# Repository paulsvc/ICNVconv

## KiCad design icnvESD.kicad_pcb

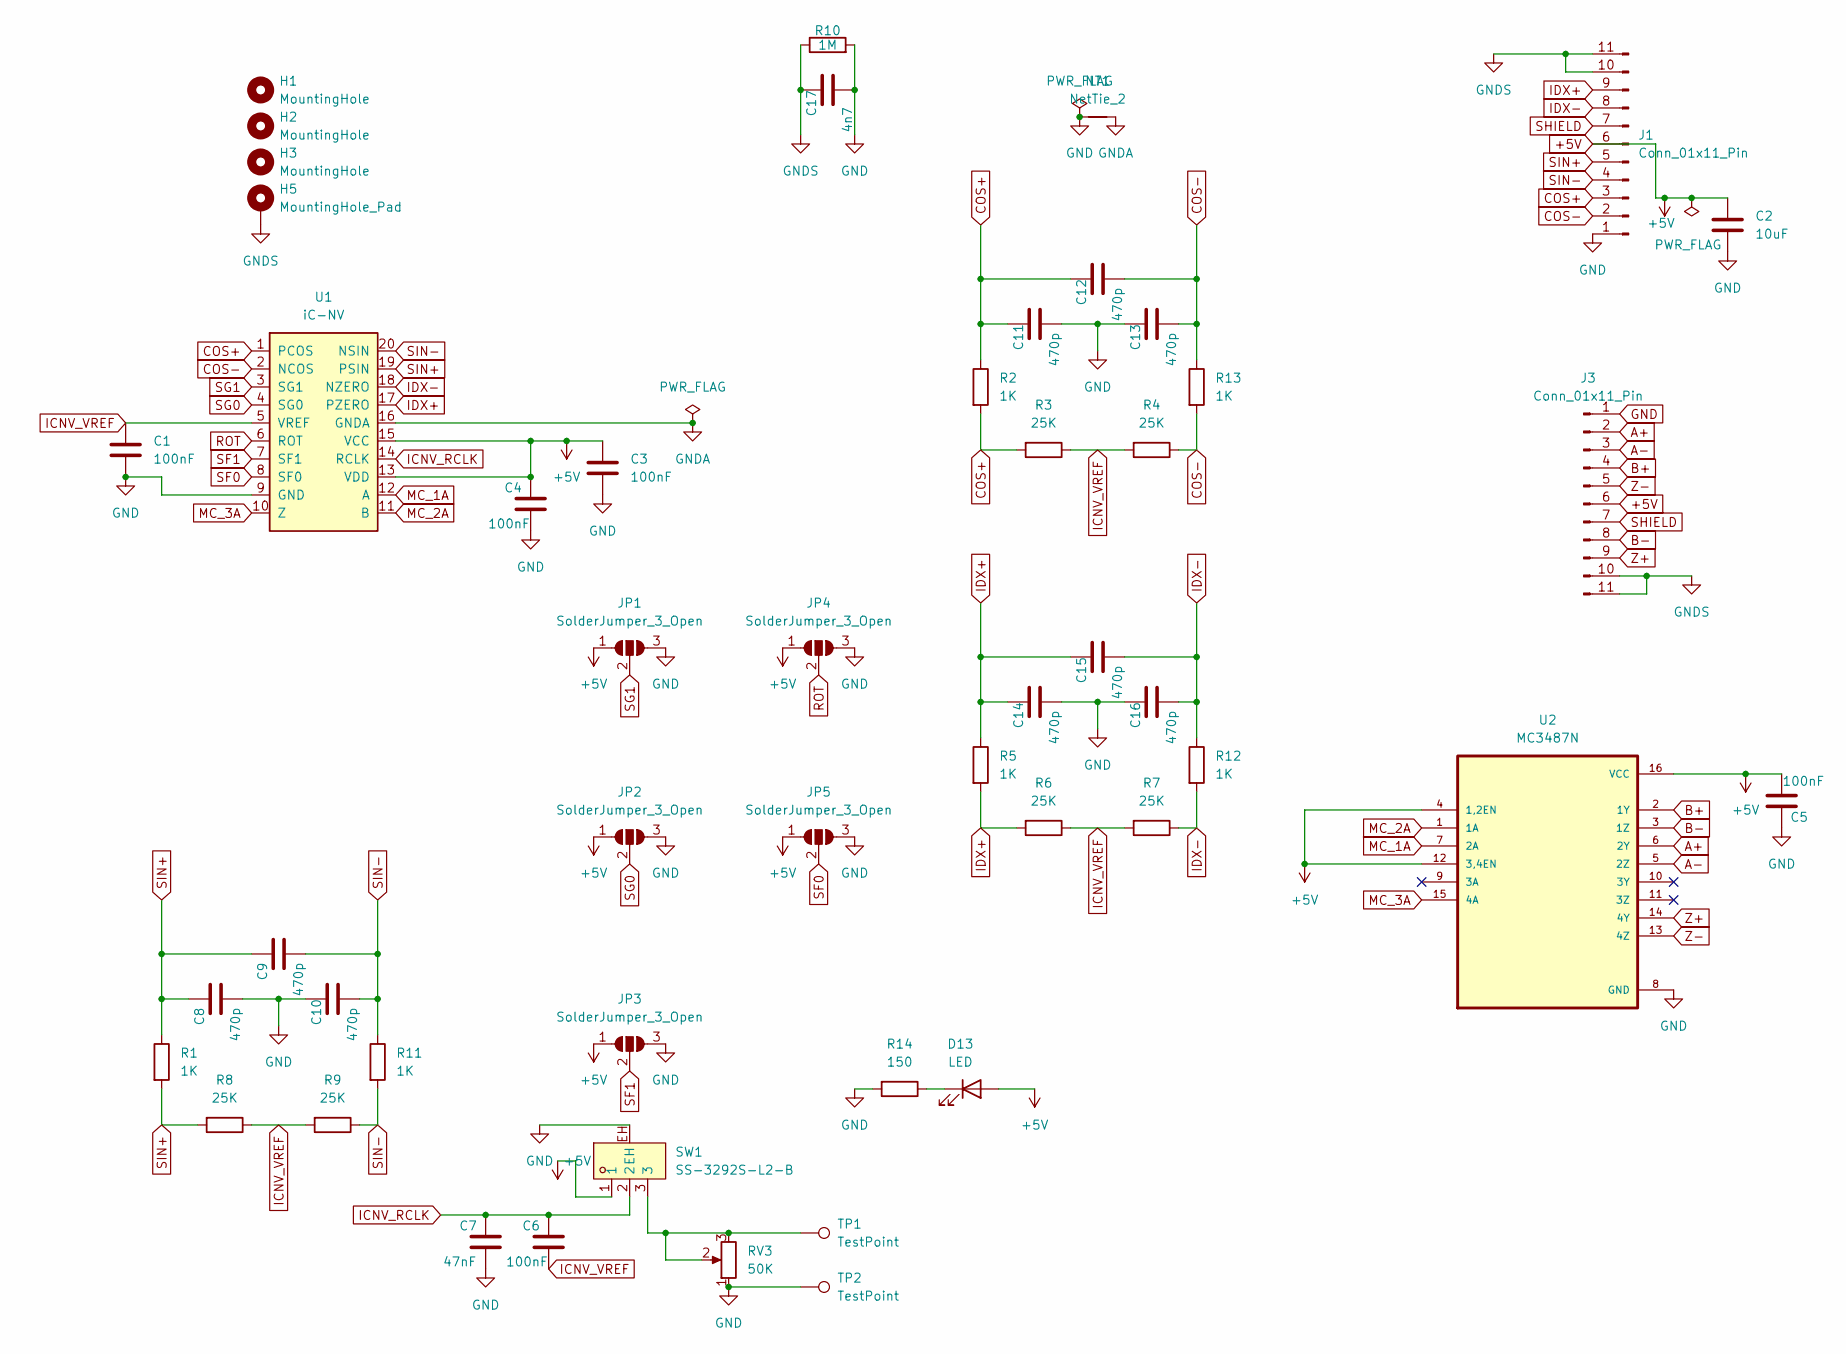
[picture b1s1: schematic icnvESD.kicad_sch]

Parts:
C1, C3, C4, C5, C6: 100nF; C_0603_1608Metric_Pad1.08x0.95mm_HandSolder
C2: 10uF; C_0603_1608Metric_Pad1.08x0.95mm_HandSolder
C7: 47nF; C_0603_1608Metric_Pad1.08x0.95mm_HandSolder
C8, C9, C10, C11, C12, C13, C14, C15, C16: 470p; C_0603_1608Metric_Pad1.08x0.95mm_HandSolder
C17: 4n7; C_0603_1608Metric_Pad1.08x0.95mm_HandSolder
D13: LED; LED_0805_2012Metric_Pad1.15x1.40mm_HandSolder
H1, H2, H3: MountingHole; MountingHole_3.2mm_M3
H5: MountingHole_Pad; MountingHole_3.2mm_M3_Pad
J1, J3: Conn_01x11_Pin; DB9-TH_D-SUB-DR-9PCM-CB
JP1, JP2, JP3, JP4, JP5: SolderJumper_3_Open; SolderJumper-3_P1.3mm_Open_Pad1.0x1.5mm
NT1: NetTie_2; NetTie-2_SMD_Pad2.0mm
R1, R2, R5, R11, R12, R13: 1K; R_0603_1608Metric_Pad0.98x0.95mm_HandSolder
R3, R4, R6, R7, R8, R9: 25K; R_0603_1608Metric_Pad0.98x0.95mm_HandSolder
R10: 1M; R_0603_1608Metric_Pad0.98x0.95mm_HandSolder
R14: 150; R_0603_1608Metric_Pad0.98x0.95mm_HandSolder
RV3: 50K; RES-ADJ-SMD_TC33X-2-104E
SW1: SS-3292S-L2-B; SW-SMD_SS-3292S-L2-B; LCSC Part C500057
TP1, TP2: TestPoint; Pin_D1.3mm_L11.0mm
U1: iC-NV; TSSOP-20_4.4x6.5mm_P0.65mm
U2: MC3487N; SOIC-16_L9.9-W3.9-P1.27-LS6.0-BL

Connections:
+5V: C2.1, C3.1, C4.1, C5.2, D13.2 (A), J1.6, J3.6, JP1.1 (A), JP2.1 (A), JP3.1 (A), JP4.1 (A), JP5.1 (A), SW1.1, U1.13 (VDD), U1.15 (VCC), U2.4 (1,2EN), U2.12 (3,4EN), U2.16 (VCC)
A+: J3.2, U2.6 (2Y)
A-: J3.3, U2.5 (2Z)
B+: J3.4, U2.2 (1Y)
B-: J3.8, U2.3 (1Z)
COS+: C11.1, C12.1, J1.3, R2.1, R2.2, R3.2, U1.1 (PCOS)
COS-: C12.2, C13.2, J1.2, R4.1, R13.1, R13.2, U1.2 (NCOS)
GND: C1.2, C2.2, C3.2, C4.2, C5.1, C7.2, C8.2, C10.1, C11.2, C13.1, C14.2, C16.1, C17.2, J1.1, J3.1, JP1.3 (B), JP2.3 (B), JP3.3 (B), JP4.3 (B), JP5.3 (B), NT1.1, R10.2, R14.2, RV3.1, SW1.EH, TP2.1, U1.9 (GND), U2.8 (GND)
GNDA: NT1.2, U1.16 (GNDA)
GNDS: C17.1, H5.1, J1.10, J1.11, J3.10, J3.11, R10.1
ICNV_RCLK: C6.1, C7.1, SW1.2, U1.14 (RCLK)
ICNV_VREF: C1.1, C6.2, R3.1, R4.2, R6.1, R7.2, R8.1, R9.2, U1.5 (VREF)
IDX+: C14.1, C15.1, J1.9, R5.1, R5.2, R6.2, U1.17 (PZERO)
IDX-: C15.2, C16.2, J1.8, R7.1, R12.1, R12.2, U1.18 (NZERO)
MC_1A: U1.12 (A), U2.7 (2A)
MC_2A: U1.11 (B), U2.1 (1A)
MC_3A: U1.10 (Z), U2.15 (4A)
unnamed: D13.1 (K), R14.1
unnamed: RV3.2, RV3.3, SW1.3, TP1.1
ROT: JP4.2 (C), U1.6 (ROT)
SF0: JP5.2 (C), U1.8 (SF0)
SF1: JP3.2 (C), U1.7 (SF1)
SG0: JP2.2 (C), U1.4 (SG0)
SG1: JP1.2 (C), U1.3 (SG1)
SHIELD: J1.7, J3.7
SIN+: C8.1, C9.1, J1.5, R1.1, R1.2, R8.2, U1.19 (PSIN)
SIN-: C9.2, C10.2, J1.4, R9.1, R11.1, R11.2, U1.20 (NSIN)
Z+: J3.9, U2.14 (4Y)
Z-: J3.5, U2.13 (4Z)

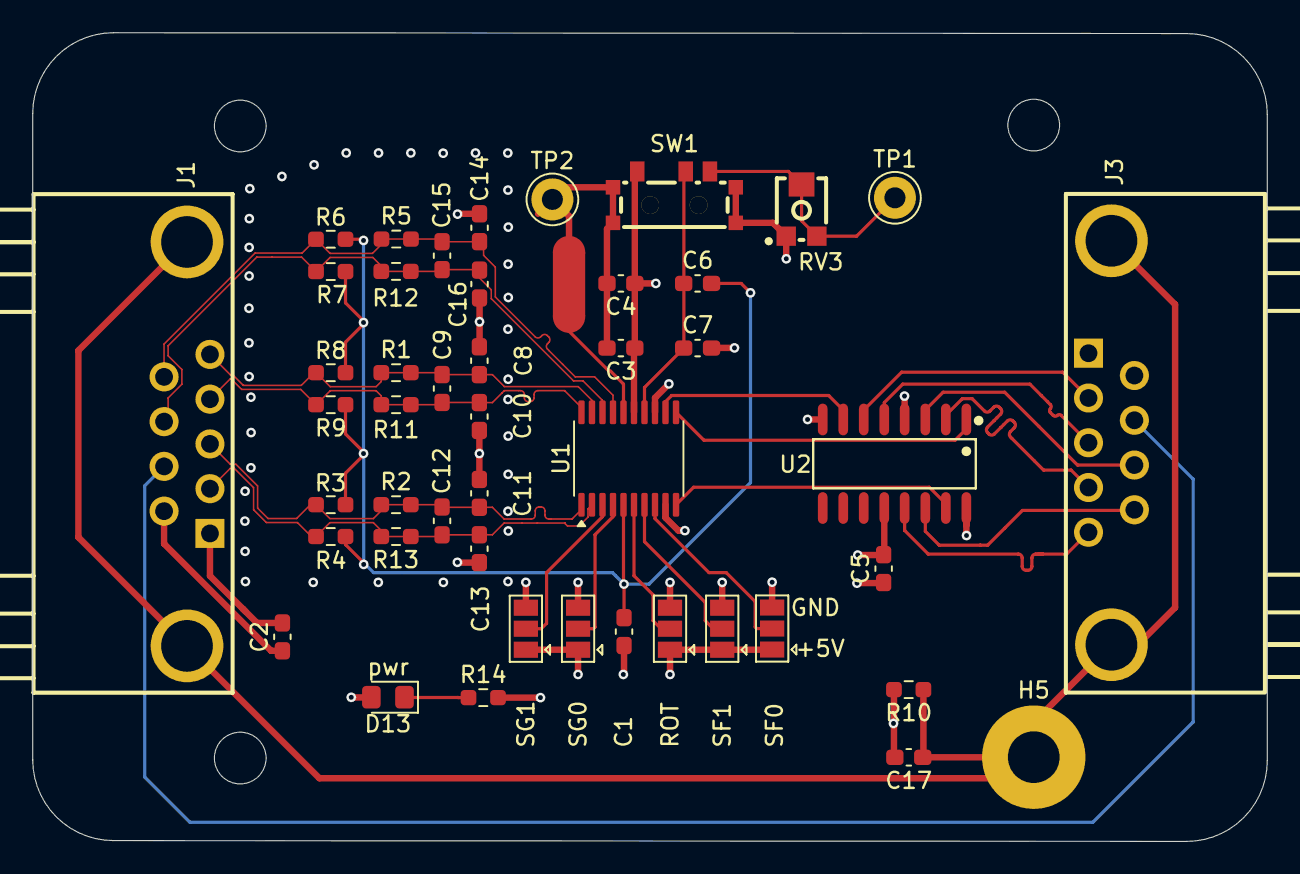
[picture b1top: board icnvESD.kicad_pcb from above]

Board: 4 copper layers, 76.4 x 50.1 mm, 50 parts (0 on the bottom side), 29 nets.

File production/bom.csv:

Designator,Footprint,Quantity,Value,LCSC Part #
"C1, C3, C4, C5, C6",0603,5,100nF,C14663
"C10, C11, C12, C13, C14, C15, C16, C8, C9",0603,9,470p,C1620
C17,0603,1,4n7,C1623
C2,0603,1,10uF,C19702
C7,0603,1,47nF,C1622
D13,0805,1,LED,
J1,DB9-TH_D-SUB-DR-9PCM-CB,1,Conn_01x11_Pin,C19077337
J3,DB9-TH_D-SUB-DR-9PCM-CB,1,Conn_01x11_Pin,C19077344
"R1, R11, R12, R13, R2, R5",0603,6,1K,C21190
R10,0603,1,1M,C22935
R14,0603,1,150,C22808
"R3, R4, R6, R7, R8, R9",0603,6,25K,C2828637
RV3,RES-ADJ-SMD_TC33X-2-104E,1,50K,C913246
SW1,SW-SMD_SS-3292S-L2-B,1,SS-3292S-L2-B,C500057
"TP1, TP2",Pin_D1.3mm_L11.0mm,2,TestPoint,
U1,TSSOP-20_4.4x6.5mm_P0.65mm,1,iC-NV,C5240841
U2,SOIC-16_L9.9-W3.9-P1.27-LS6.0-BL,1,MC3487N,C7309

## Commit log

2026-03-17 ibom
